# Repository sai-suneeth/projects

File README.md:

for the proteus simulations download the mkv files

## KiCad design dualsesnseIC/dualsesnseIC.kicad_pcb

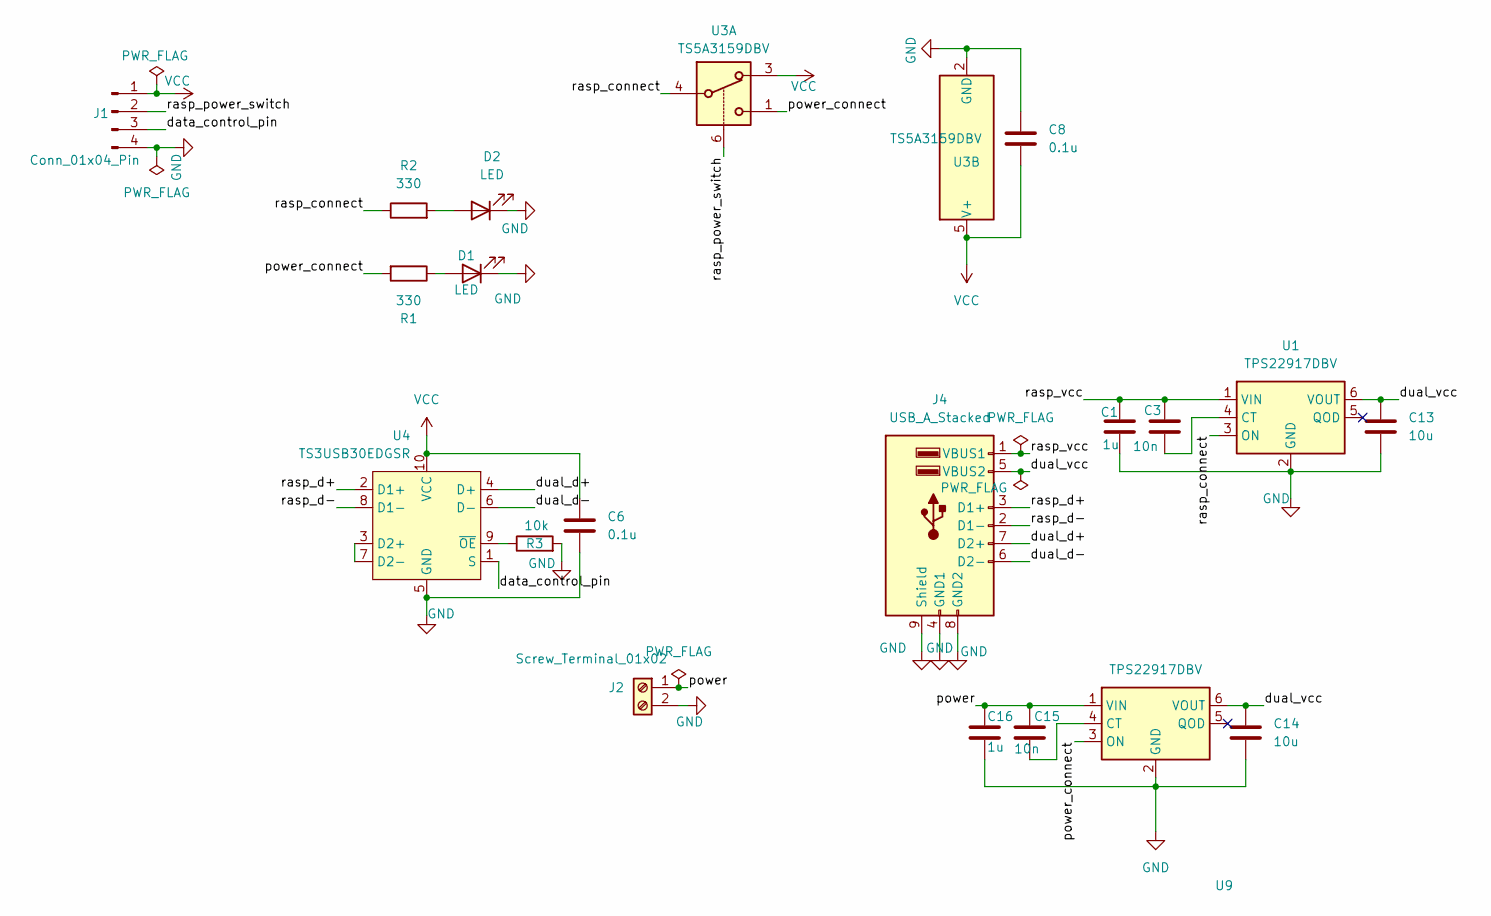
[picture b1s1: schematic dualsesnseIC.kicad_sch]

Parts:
C1, C16: 1u; C_0603_1608Metric
C3, C15: 10n; C_0603_1608Metric
C6: 0.1u; C_0603_1608Metric
C8: 0.1u; C_0603_1608Metric_Pad1.08x0.95mm_HandSolder
C13, C14: 10u; C_0603_1608Metric
D1, D2: LED; LED_0201_0603Metric
J1: Conn_01x04_Pin; PinHeader_1x04_P2.54mm_Vertical
J2: Screw_Terminal_01x02; TerminalBlock_CUI_TB007-508-02_1x02_P5.08mm_Horizontal
J4: USB_A_Stacked; USB_A_CUI_UJ2-ADH-TH_Horizontal_Stacked
R1, R2: 330; R_0603_1608Metric
R3: 10k; R_0603_1608Metric
U1, U9: TPS22917DBV; SOT-23-6_Handsoldering
U3: TS5A3159DBV; SOT-23-6
U4: TS3USB30EDGSR; VSSOP-10_3x3mm_P0.5mm

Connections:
/data_control_pin: J1.3, U4.1 (S)
/dual_d+: J4.7 (D2+), U4.4 (D+)
/dual_d-: J4.6 (D2-), U4.6 (D-)
/dual_vcc: C13.1, C14.1, J4.5 (VBUS2), U1.6 (VOUT), U9.6 (VOUT)
/power: C15.1, C16.1, J2.1, U9.1 (VIN)
/power_connect: R1.2, U3.1, U9.3 (ON)
/rasp_connect: R2.1, U1.3 (ON), U3.4
/rasp_d+: J4.3 (D1+), U4.2 (D1+)
/rasp_d-: J4.2 (D1-), U4.8 (D1-)
/rasp_power_switch: J1.2, U3.6
/rasp_vcc: C1.1, C3.1, J4.1 (VBUS1), U1.1 (VIN)
GND: C1.2, C6.2, C8.1, C13.2, C14.2, C16.2, D1.1 (K), D2.1 (K), J1.4, J2.2, J4.4 (GND1), J4.8 (GND2), J4.9 (Shield), R3.2, U1.2 (GND), U3.2 (GND), U4.5 (GND), U9.2 (GND)
unnamed: D1.2 (A), R1.1
unnamed: D2.2 (A), R2.2
unnamed: C3.2, U1.4 (CT)
unnamed: U4.3 (D2+), U4.7 (D2-)
unnamed: R3.1, U4.9 (~OE)
unnamed: C15.2, U9.4 (CT)
VCC: C6.1, C8.2, J1.1, U3.3, U3.5 (V+), U4.10 (VCC)

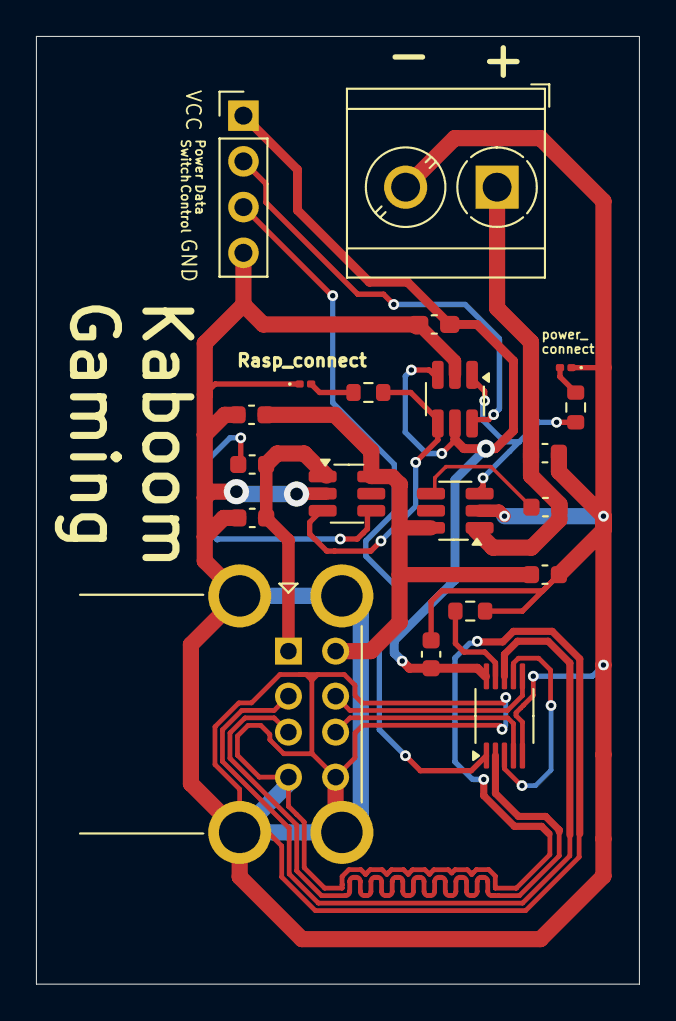
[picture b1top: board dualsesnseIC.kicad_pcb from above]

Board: 2 copper layers, 33.5 x 52.7 mm, 20 parts (0 on the bottom side), 19 nets.

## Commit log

2025-11-05 Create snake-game(hard-wired)
2025-11-05 snake-game(hard-wired)
2025-11-05 Rename 'st' to 'stm32' in workspace directory
2025-11-05 Create codes
2025-11-05 Create raspberrypi
2025-11-05 Update raspberrypi
2026-02-01 Initial commit: Add KiCAD project files
2026-02-01 final_update
2026-02-01 Create proteus
2026-02-01 Update README with video download instructions
    Added instructions to download the simulation video.
2026-02-06 added twiddle factor generator
2026-02-22 updated_files
